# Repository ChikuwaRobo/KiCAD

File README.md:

# KiCAD
対応:User/Documents/KiCAD  
ユーザーライブラリを複数バージョンまとめて管理するためのリポジトリ｡

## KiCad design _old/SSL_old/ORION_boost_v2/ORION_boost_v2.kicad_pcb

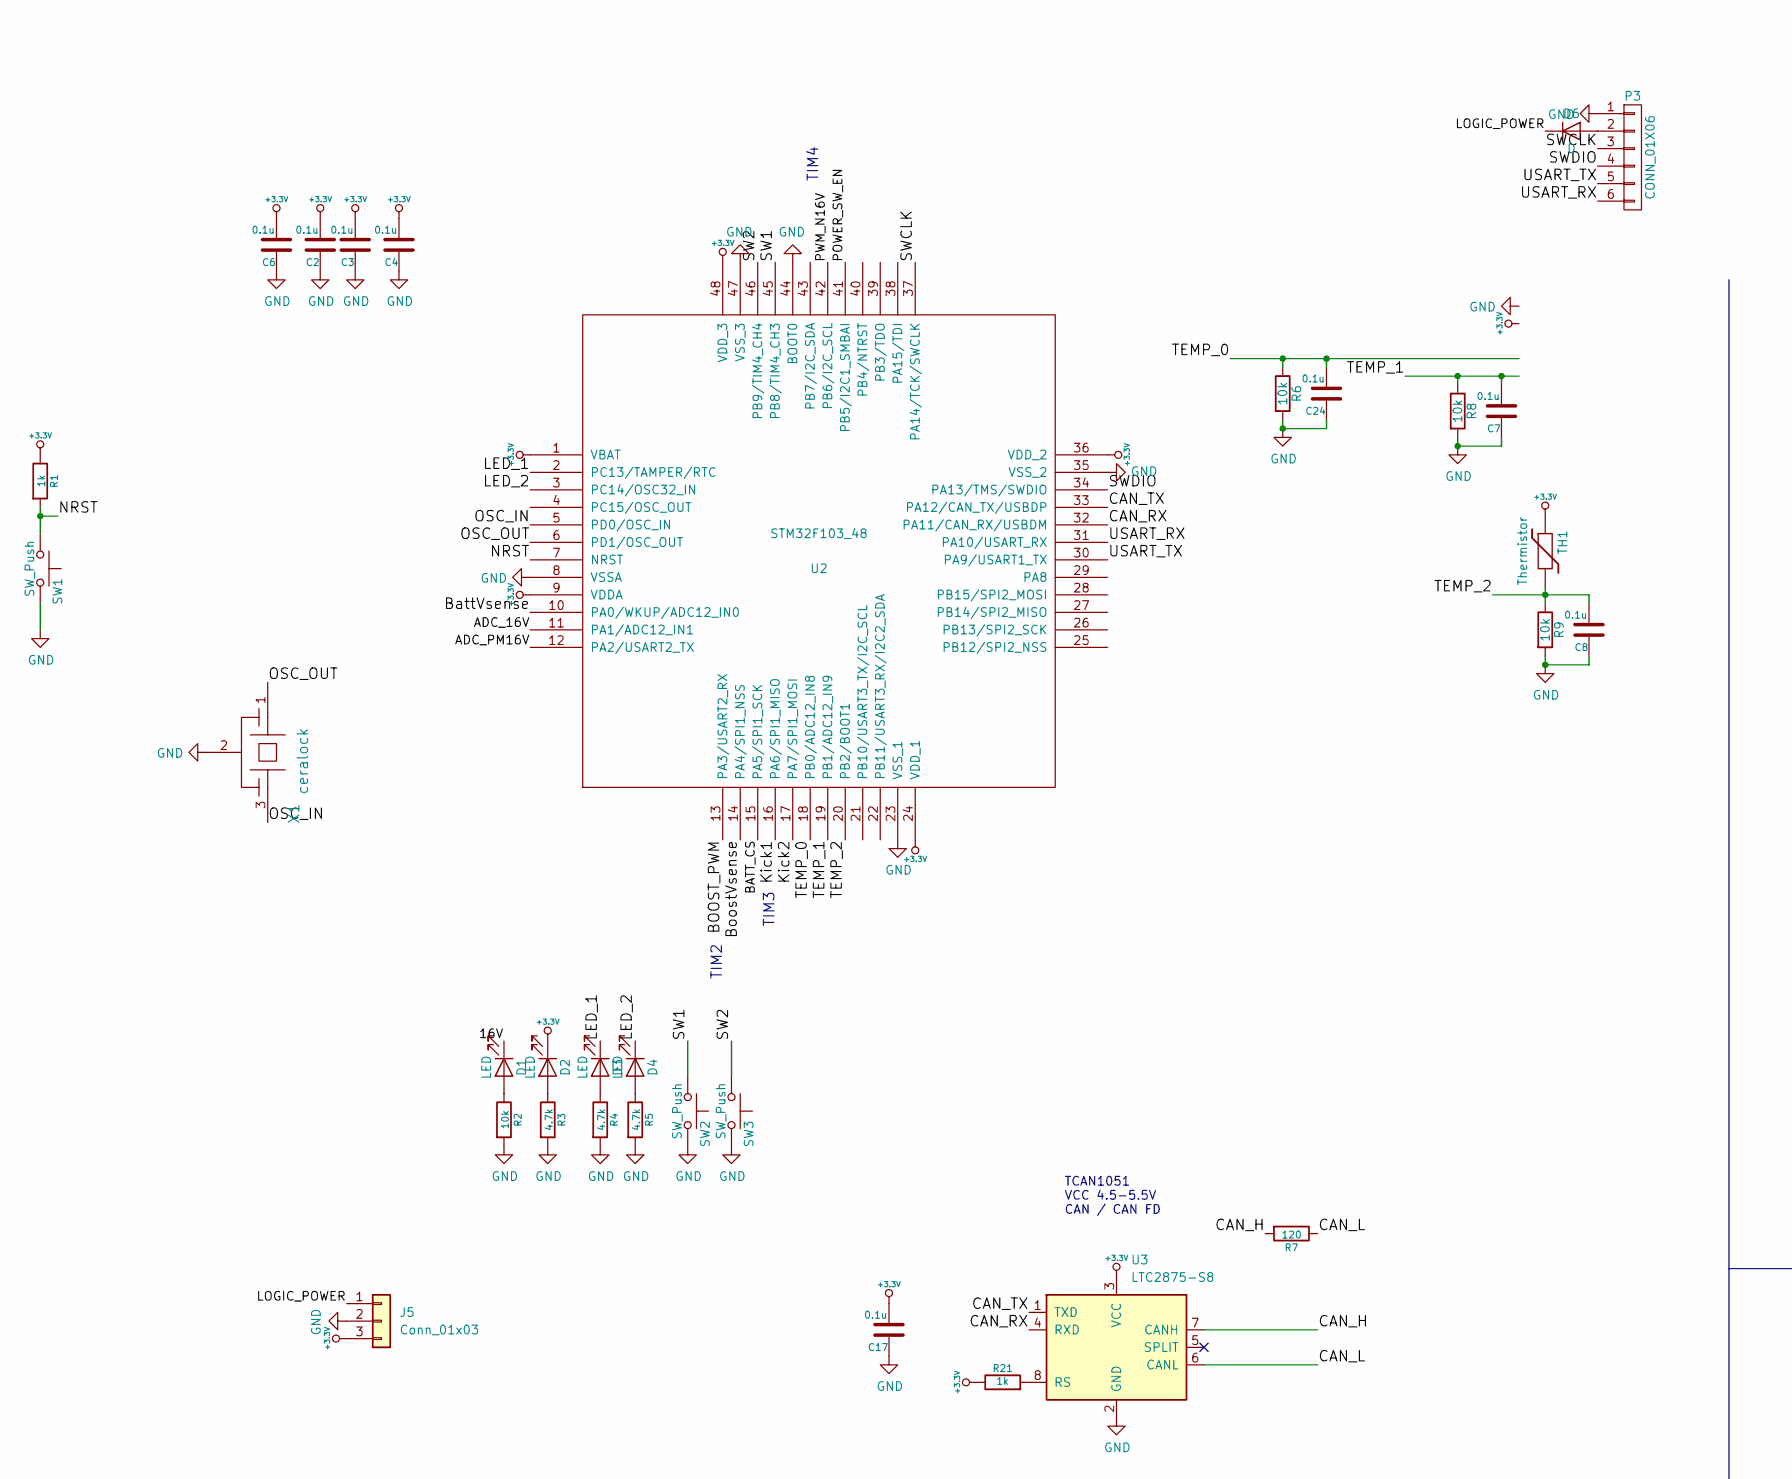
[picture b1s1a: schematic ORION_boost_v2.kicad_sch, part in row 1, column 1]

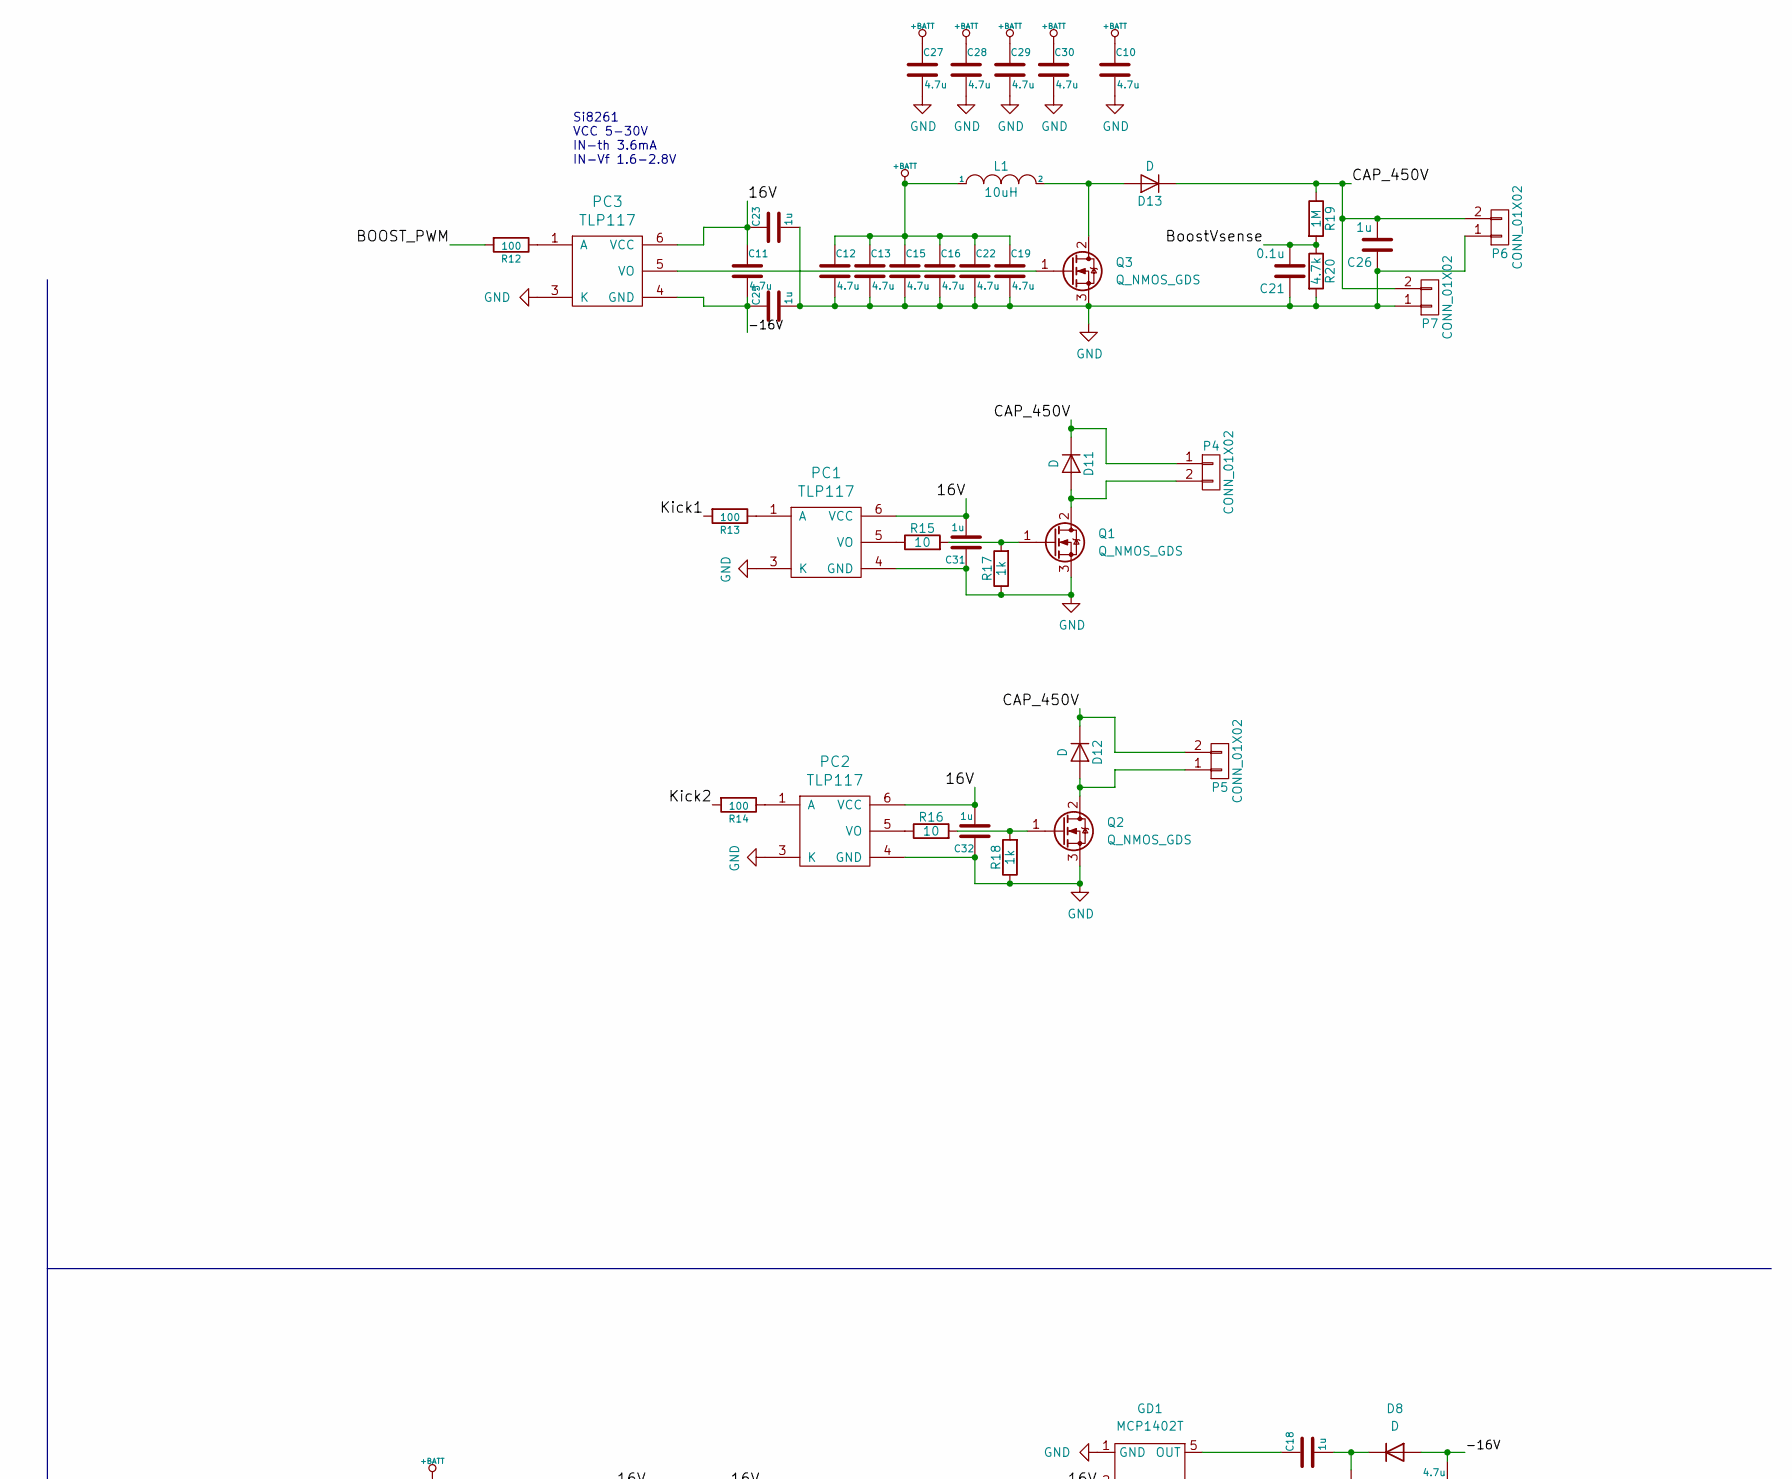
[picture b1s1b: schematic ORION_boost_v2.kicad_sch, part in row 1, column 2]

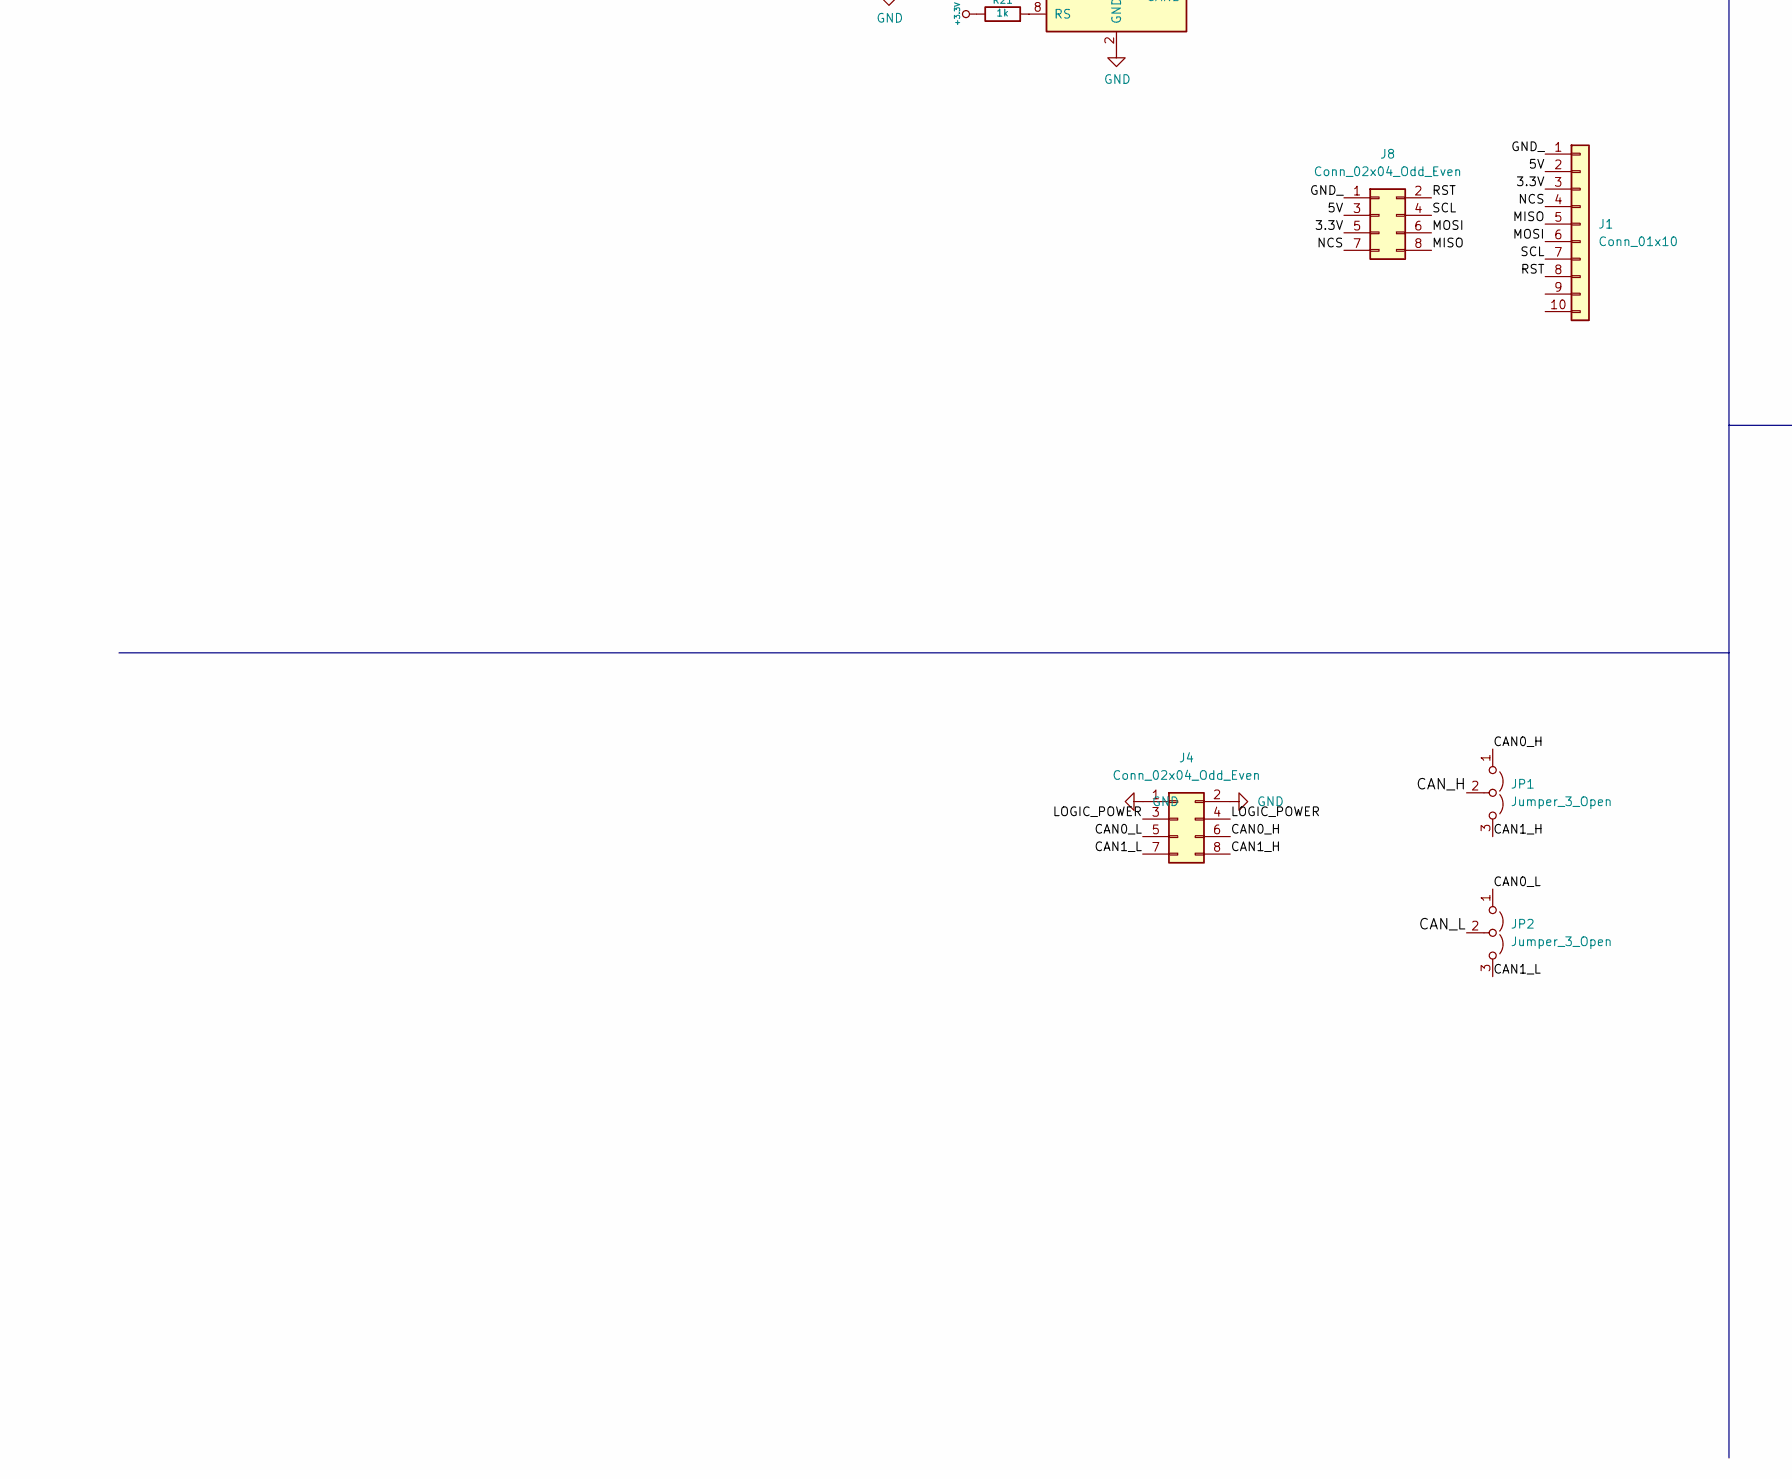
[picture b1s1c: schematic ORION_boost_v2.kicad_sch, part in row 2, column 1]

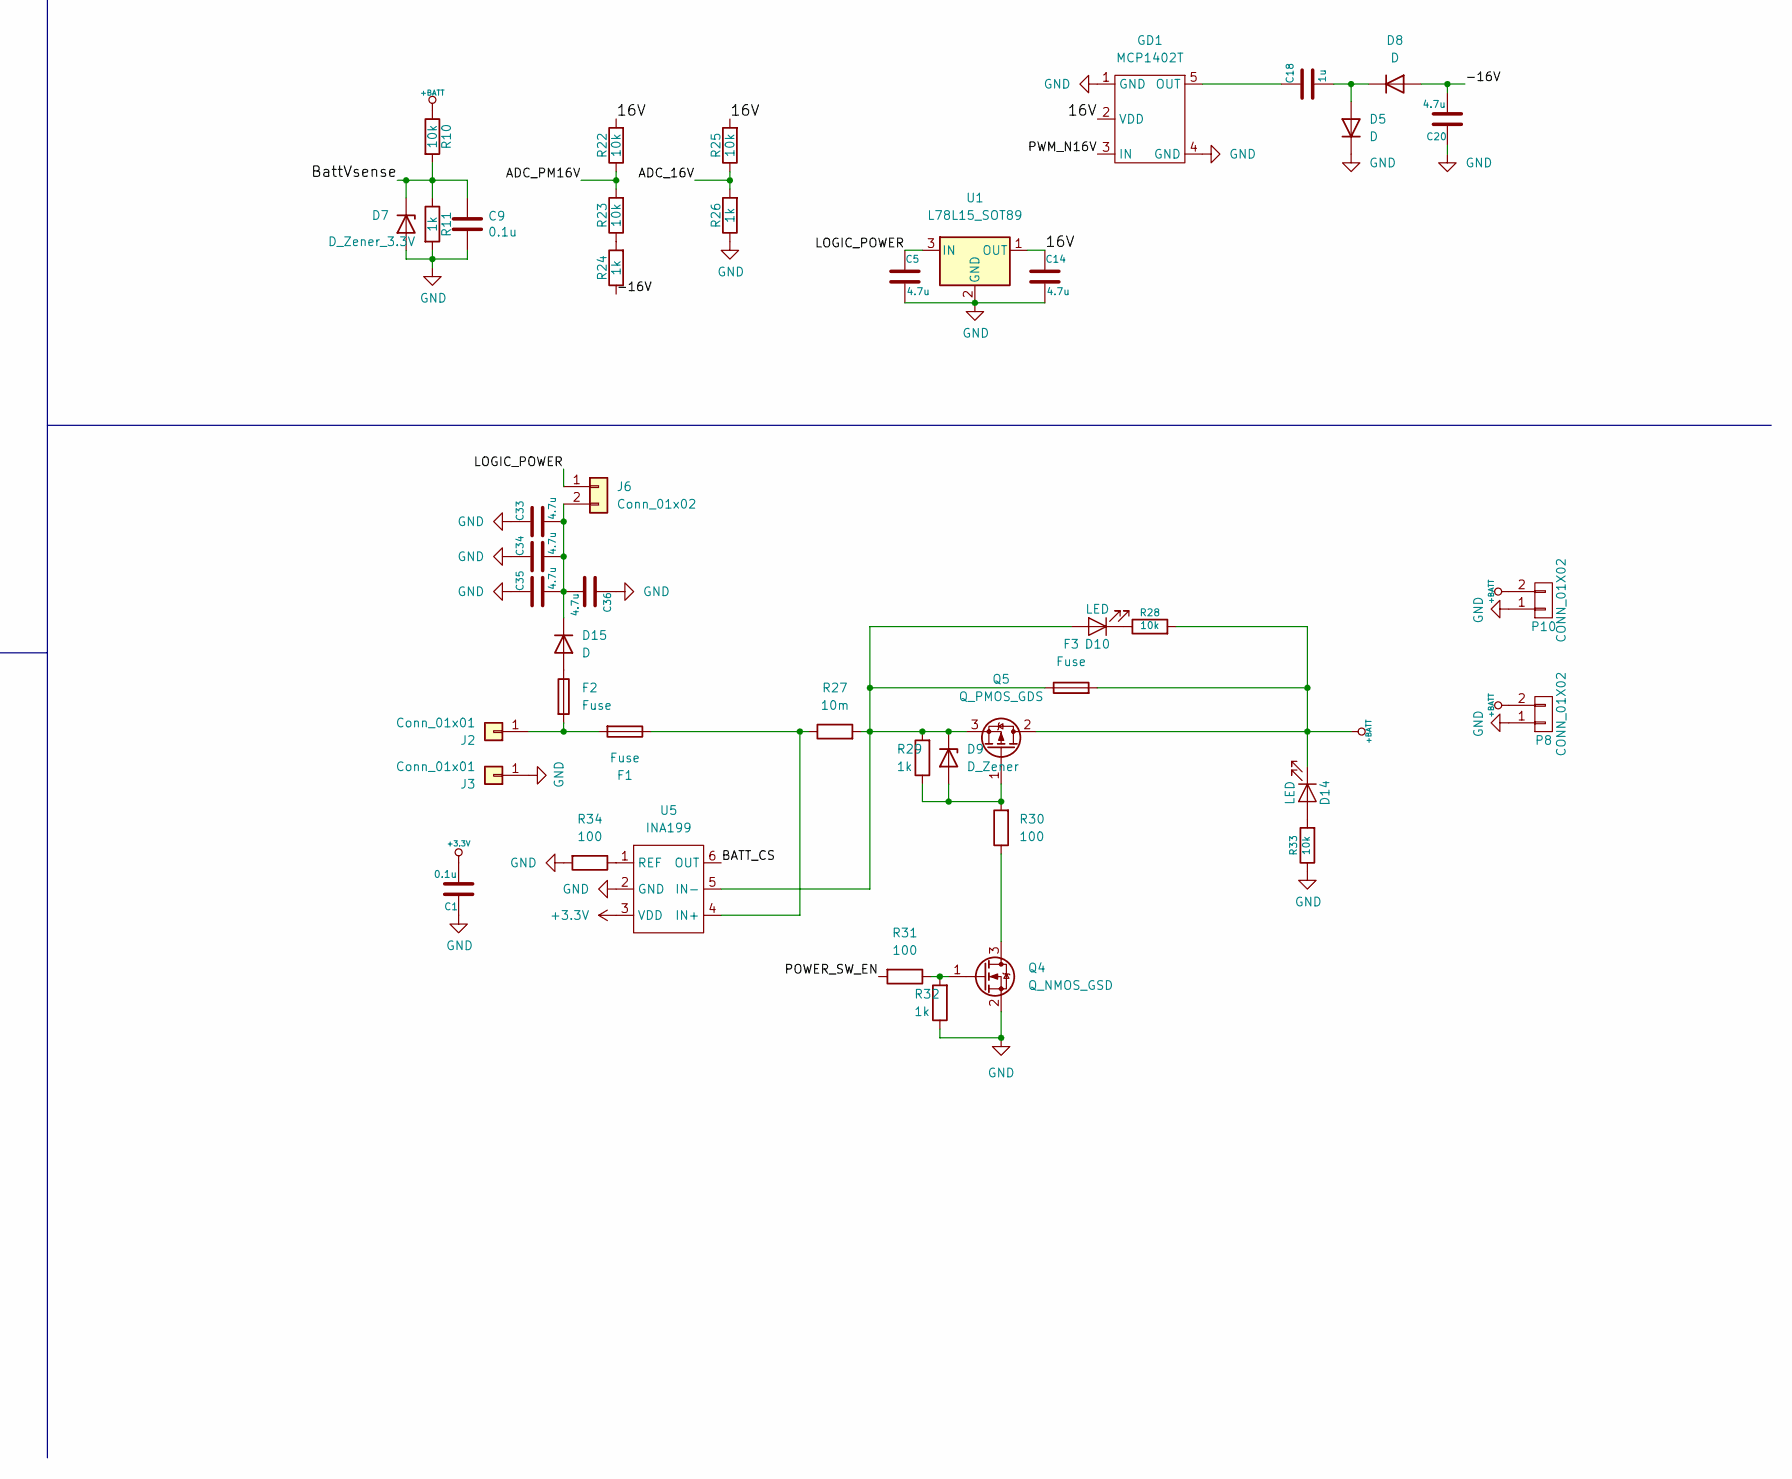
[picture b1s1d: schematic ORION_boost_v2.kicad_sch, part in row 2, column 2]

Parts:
C1, C2, C3, C4, C6, C7, C8, C9, C17, C21, C24: 0.1u; C_0603_1608Metric
C5, C10, C11, C14, C15, C16, C19, C20, C22, C27, C28, C29, C30, C33, C34, C35, C36: 4.7u; C_1206_3216Metric
C12, C13: 4.7u; CP_Radial_D10.0mm_P5.00mm
C18, C23, C25, C31, C32: 1u; C_0603_1608Metric
C26: 1u; C_Rect_L16.5mm_W5.0mm_P15.00mm_MKT
D1, D2, D3, D4, D10, D14: LED; LED_0603_1608Metric
D5, D6, D8: D; D_0603_1608Metric
D7: D_Zener_3.3V; D_0603_1608Metric
D9: D_Zener; D_0603_1608Metric_Pad1.05x0.95mm_HandSolder
D11, D12, D13: D; TO-252-2-RD
D15: D; D_MiniMELF
F1: Fuse; Reusable_Breaker_Top
F2, F3: Fuse; Fuse_1210_3225Metric
GD1: MCP1402T; SOT-23-5
J1: Conn_01x10; PinSocket_1x10_P2.54mm_Vertical
J2, J3: Conn_01x01; TestPoint_Plated_Hole_D4.0mm
J4, J8: Conn_02x04_Odd_Even; Hirose_DF11-8DP-2DSA_2x04_P2.00mm_Vertical
J5: Conn_01x03; VX07805-500
J6: Conn_01x02; JST_PH_B2B-PH-K_1x02_P2.00mm_Vertical
JP1, JP2: Jumper_3_Open; SolderJumper-3_P1.3mm_Open_RoundedPad1.0x1.5mm
L1: 10uH; L_Bourns_SRP1770TA_16.9x16.9mm
P3: CONN_01X06; ZH_B6B-ZR
P4, P5, P6, P7: CONN_01X02; Hirose_DF63M-2P-3.96DSA_1x02_P3.96mm_Vertical_pinless
P8, P10: CONN_01X02; AMASS_XT30U-M_1x02_P5.0mm_Vertical
PC1, PC2, PC3: TLP117; MFSOP6-5_4.4x3.6mm_P1.27mm
Q1, Q2: Q_NMOS_GDS; TO-252-2
Q3: Q_NMOS_GDS; TO-220F-3_Horizontal_TabDown_HV
Q4: Q_NMOS_GSD; SOT-23
Q5: Q_PMOS_GDS; TO-252-2
R1, R11, R17, R18, R24, R26, R29, R32: 1k; R_0603_1608Metric
R2, R28, R33: 10k; R_0603_1608Metric_Pad0.98x0.95mm_HandSolder
R3, R4, R5, R20: 4.7k; R_0603_1608Metric
R6, R8, R9, R10, R22, R23, R25: 10k; R_0603_1608Metric
R7: 120; R_0603_1608Metric
R12: 100; R_0603_1608Metric_Pad0.98x0.95mm_HandSolder
R13, R14, R30, R31, R34: 100; R_0603_1608Metric
R15, R16: 10; R_0603_1608Metric
R19: 1M; R_1206_3216Metric
R21: 1k; R_0603_1608Metric_Pad0.98x0.95mm_HandSolder
R27: 10m; R_1020_2550Metric
SW1, SW2, SW3: SW_Push; SW_Push_1P1T_NO_CK_KMR2
TH1: Thermistor; R_0603_1608Metric
U1: L78L15_SOT89; SOT-89-3
U2: STM32F103_48; LQFP-48_7x7mm_P0.5mm
U3: LTC2875-S8; SOIC-8_3.9x4.9mm_P1.27mm
U5: INA199; SOT-23-6
X1: ceralock; Resonator_SMD_Murata_CSTxExxV-3Pin_3.0x1.1mm

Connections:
+3.3V: C1.2, C2.2, C3.2, C4.2, C6.2, C17.2, D2.1 (K), J5.3, R1.1, R21.1, TH1.1, U2.1 (VBAT), U2.9 (VDDA), U2.24 (VDD_1), U2.36 (VDD_2), U2.48 (VDD_3), U3.3 (VCC), U5.3 (VDD)
+BATT: C10.1, C12.1, C13.1, C15.1, C16.1, C19.1, C22.1, C27.1, C28.1, C29.1, C30.1, D14.1 (K), F3.2, L1.1, P8.2, P10.2, Q5.2 (D), R10.1, R28.2
/3.3V: J1.3, J8.5
/5V: J1.2, J8.3
/16V: C11.1, C14.1, C23.1, C31.2, C32.2, D1.1 (K), GD1.2 (VDD), PC1.6 (VCC), PC2.6 (VCC), PC3.6 (VCC), R22.2, R25.2, U1.1 (OUT)
/-16V: C11.2, C20.2, C25.1, D8.2 (A), PC3.4 (GND), R24.1
/ADC_16V: R25.1, R26.2, U2.11 (PA1/ADC12_IN1)
/ADC_PM16V: R22.1, R23.2, U2.12 (PA2/USART2_TX)
/BATT_CS: U2.15 (PA5/SPI1_SCK), U5.6 (OUT)
/BOOST_PWM: R12.2, U2.13 (PA3/USART2_RX)
/BattVsense: C9.2, D7.1 (K), R10.2, R11.1, U2.10 (PA0/WKUP/ADC12_IN0)
/BoostVsense: C21.2, R19.2, R20.1, U2.14 (PA4/SPI1_NSS)
/CAN0_H: J4.6, JP1.1 (A)
/CAN0_L: J4.5, JP2.1 (A)
/CAN1_H: J4.8, JP1.3 (B)
/CAN1_L: J4.7, JP2.3 (B)
/CAN_H: JP1.2 (C), R7.2, U3.7 (CANH)
/CAN_L: JP2.2 (C), R7.1, U3.6 (CANL)
/CAN_RX: U2.32 (PA11/CAN_RX/USBDM), U3.4 (RXD)
/CAN_TX: U2.33 (PA12/CAN_TX/USBDP), U3.1 (TXD)
/CAP_450V: C26.2, D11.1 (K), D12.1 (K), D13.1 (K), P4.1, P5.2, P6.2, P7.2, R19.1
/GND_: J1.1, J8.1
/Kick1: R13.2, U2.16 (PA6/SPI1_MISO)
/Kick2: R14.2, U2.17 (PA7/SPI1_MOSI)
/LED_1: D3.1 (K), U2.2 (PC13/TAMPER/RTC)
/LED_2: D4.1 (K), U2.3 (PC14/OSC32_IN)
/LOGIC_POWER: C5.1, D6.1 (K), J4.3, J4.4, J5.1, J6.1, U1.3 (IN)
/MISO: J1.5, J8.8
/MOSI: J1.6, J8.6
/NCS: J1.4, J8.7
/NRST: R1.2, SW1.1, U2.7 (NRST)
/OSC_IN: U2.5 (PD0/OSC_IN), X1.3
/OSC_OUT: U2.6 (PD1/OSC_OUT), X1.1
/POWER_SW_EN: R31.2, U2.41 (PB5/I2C1_SMBAI)
/PWM_N16V: GD1.3 (IN), U2.42 (PB6/I2C_SCL)
/RST: J1.8, J8.2
/SCL: J1.7, J8.4
/SW1: SW2.1, U2.45 (PB8/TIM4_CH3)
/SW2: SW3.1, U2.46 (PB9/TIM4_CH4)
/SWCLK: P3.3, U2.37 (PA14/TCK/SWCLK)
/SWDIO: P3.4, U2.34 (PA13/TMS/SWDIO)
/TEMP_0: C24.2, R6.1, U2.18 (PB0/ADC12_IN8)
/TEMP_1: C7.2, R8.1, U2.19 (PB1/ADC12_IN9)
/TEMP_2: C8.2, R9.1, TH1.2, U2.20 (PB2/BOOT1)
/USART_RX: P3.6, U2.31 (PA10/USART_RX)
/USART_TX: P3.5, U2.30 (PA9/USART1_TX)
GND: C1.1, C2.1, C3.1, C4.1, C5.2, C6.1, C7.1, C8.1, C9.1, C10.2, C12.2, C13.2, C14.2, C15.2, C16.2, C17.1, C19.2, C20.1, C21.1, C22.2, C23.2, C24.1, C25.2, C26.1, C27.2, C28.2, C29.2, C30.2, C31.1, C32.1, C33.1, C34.1, C35.1, C36.1, D5.1 (K), D7.2 (A), GD1.1 (GND), GD1.4 (GND), J3.1, J4.1, J4.2, J5.2, P3.1, P6.1, P7.1, P8.1, P10.1, PC1.3 (K), PC1.4 (GND), PC2.3 (K), PC2.4 (GND), PC3.3 (K), Q1.3 (S), Q2.3 (S), Q3.3 (S), Q4.2 (S), R2.2, R3.2, R4.2, R5.2, R6.2, R8.2, R9.2, R11.2, R17.1, R18.1, R20.2, R26.1, R32.1, R33.1, R34.2, SW1.2, SW2.2, SW3.2, U1.2 (GND), U2.8 (VSSA), U2.23 (VSS_1), U2.35 (VSS_2), U2.44 (BOOT0), U2.47 (VSS_3), U3.2 (GND), U5.2 (GND), X1.2
unnamed: C18.1, GD1.5 (OUT)
unnamed: C18.2, D5.2 (A), D8.1 (K)
unnamed: D1.2 (A), R2.1
unnamed: D2.2 (A), R3.1
unnamed: D3.2 (A), R4.1
unnamed: D4.2 (A), R5.1
unnamed: D6.2 (A), P3.2
unnamed: D9.2 (A), Q5.1 (G), R29.1, R30.2
unnamed: D10.1 (K), R28.1
unnamed: D9.1 (K), D10.2 (A), F3.1, Q5.3 (S), R27.2, R29.2, U5.5 (IN-)
unnamed: D11.2 (A), P4.2, Q1.2 (D)
unnamed: D12.2 (A), P5.1, Q2.2 (D)
unnamed: D13.2 (A), L1.2, Q3.2 (D)
unnamed: D14.2 (A), R33.2
unnamed: D15.2 (A), F2.1
unnamed: F1.1, R27.1, U5.4 (IN+)
unnamed: F1.2, F2.2, J2.1
unnamed: C33.2, C34.2, C35.2, C36.2, D15.1 (K), J6.2
unnamed: PC1.1 (A), R13.1
unnamed: PC1.5 (VO), R15.1
unnamed: PC2.1 (A), R14.1
unnamed: PC2.5 (VO), R16.1
unnamed: PC3.1 (A), R12.1
unnamed: PC3.5 (VO), Q3.1 (G)
unnamed: Q1.1 (G), R15.2, R17.2
unnamed: Q2.1 (G), R16.2, R18.2
unnamed: Q4.1 (G), R31.1, R32.2
unnamed: Q4.3 (D), R30.1
unnamed: R21.2, U3.8 (RS)
unnamed: R23.1, R24.2
unnamed: R34.1, U5.1 (REF)

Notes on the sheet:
Si8261 VCC 5-30V IN-th 3.6mA IN-Vf 1.6-2.8V
TIM3
TIM4
TCAN1051 VCC 4.5-5.5V CAN / CAN FD
TIM2

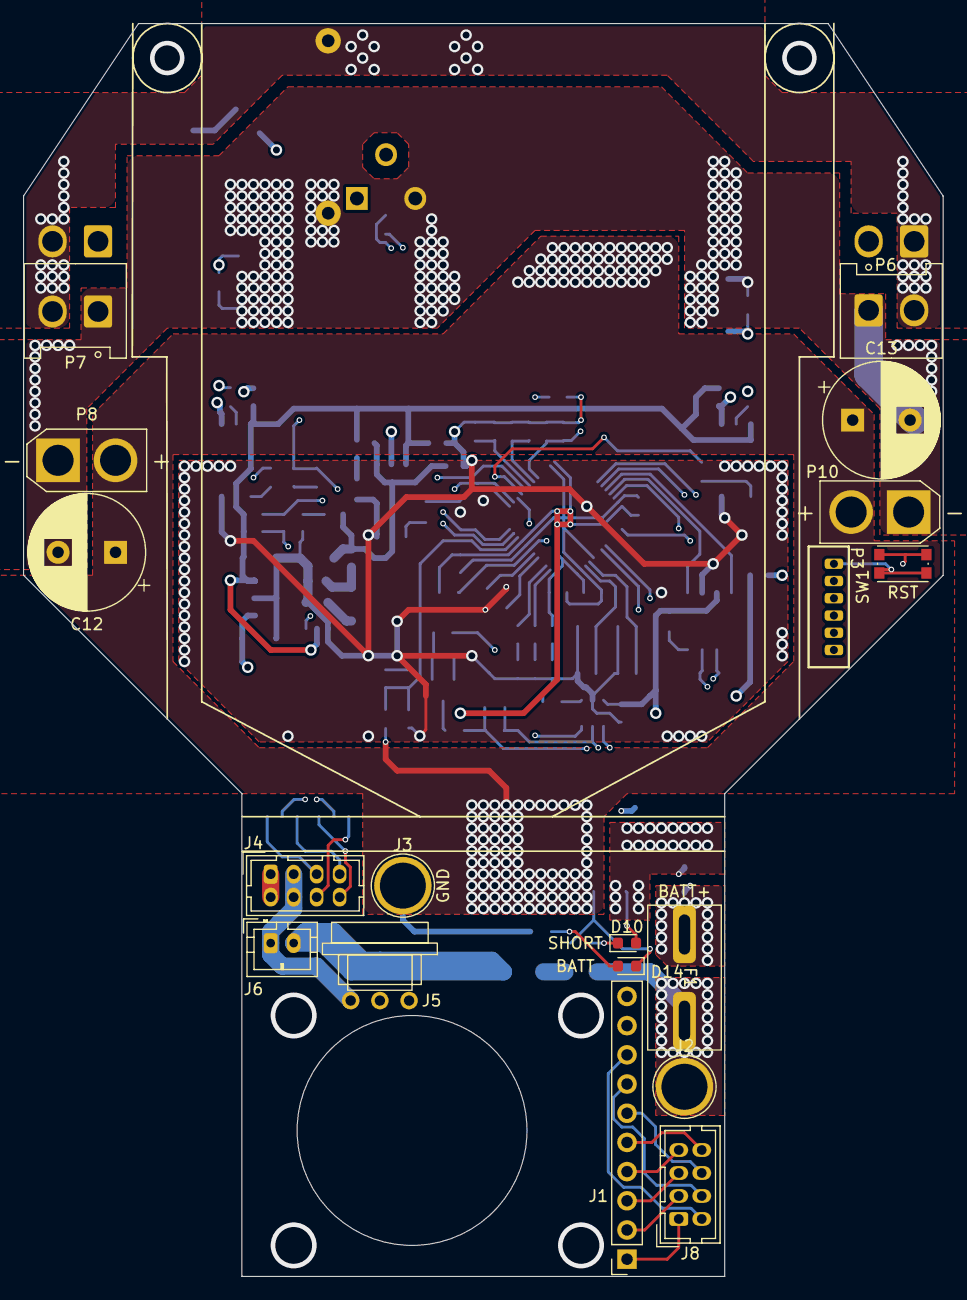
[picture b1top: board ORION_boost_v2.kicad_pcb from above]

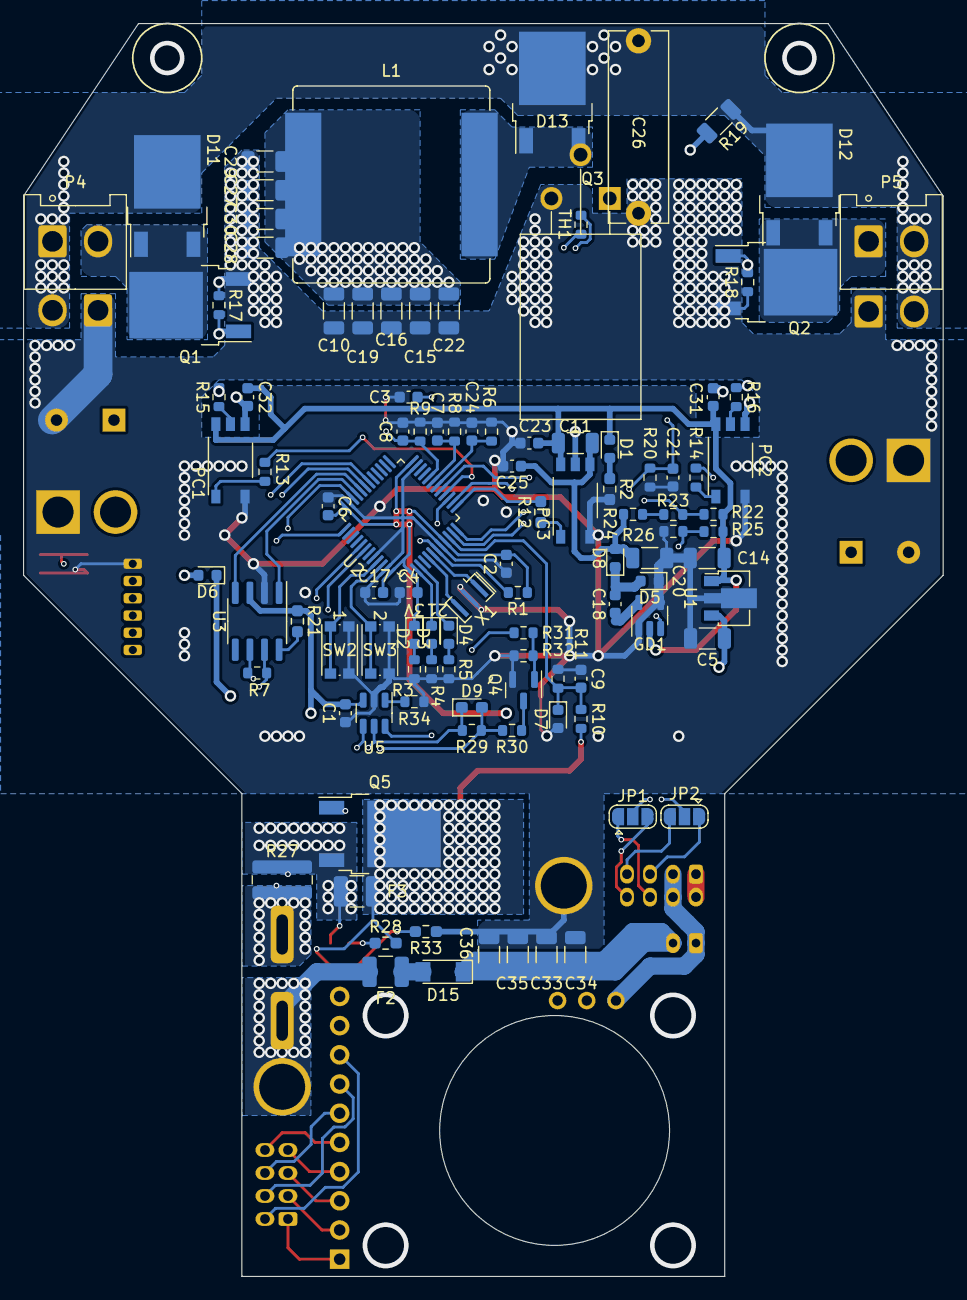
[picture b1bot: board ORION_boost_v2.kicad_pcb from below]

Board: 4 copper layers, 80.0 x 109.0 mm, 123 parts (105 on the bottom side), 78 nets.

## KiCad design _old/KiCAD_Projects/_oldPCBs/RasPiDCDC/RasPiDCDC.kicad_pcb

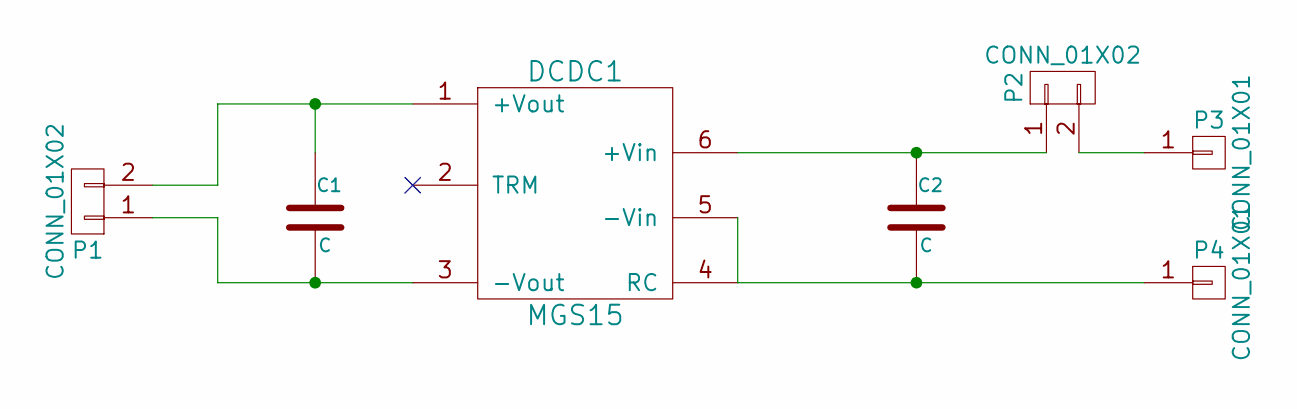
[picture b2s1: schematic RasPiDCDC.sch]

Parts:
C1, C2: C; C_Radial_D10_L20_P5
DCDC1: MGS15; MGS30
P1, P2: CONN_01X02; XA_2T
P3, P4: CONN_01X01; 1pin

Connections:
unnamed: C1.1, DCDC1.1 (+Vout), P1.2
unnamed: C1.2, DCDC1.3 (-Vout), P1.1
unnamed: C2.1, DCDC1.6 (+Vin), P2.1
unnamed: C2.2, DCDC1.4 (RC), DCDC1.5 (-Vin), P4.1
unnamed: P2.2, P3.1

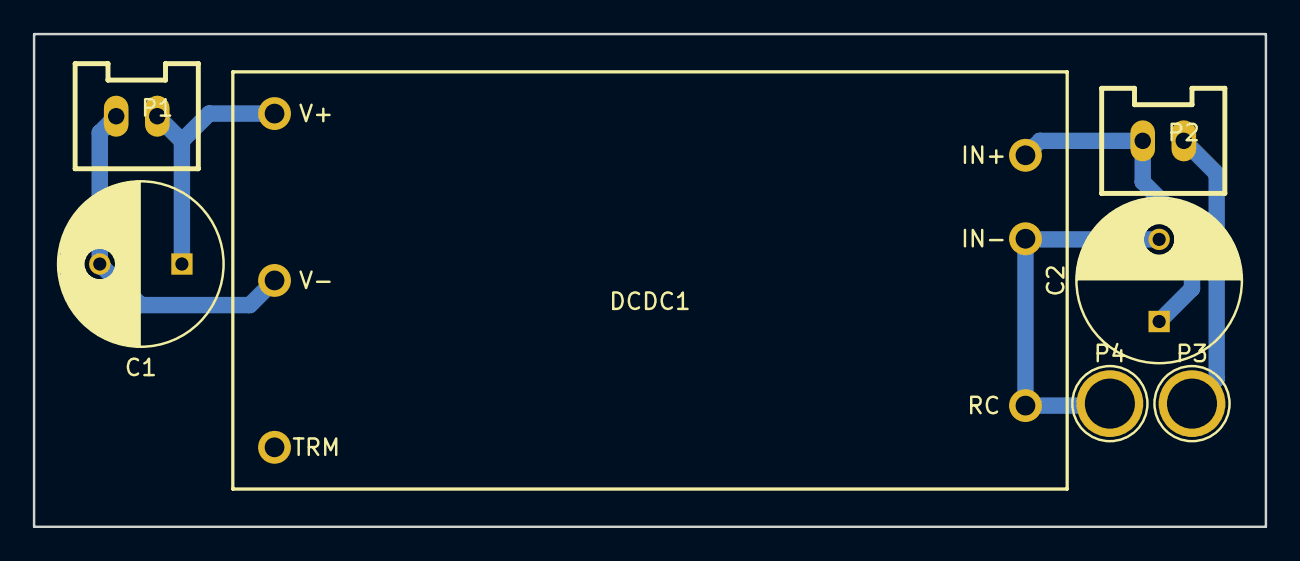
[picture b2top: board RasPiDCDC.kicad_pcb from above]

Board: 2 copper layers, 75.0 x 30.0 mm, 7 parts (0 on the bottom side), 5 nets.

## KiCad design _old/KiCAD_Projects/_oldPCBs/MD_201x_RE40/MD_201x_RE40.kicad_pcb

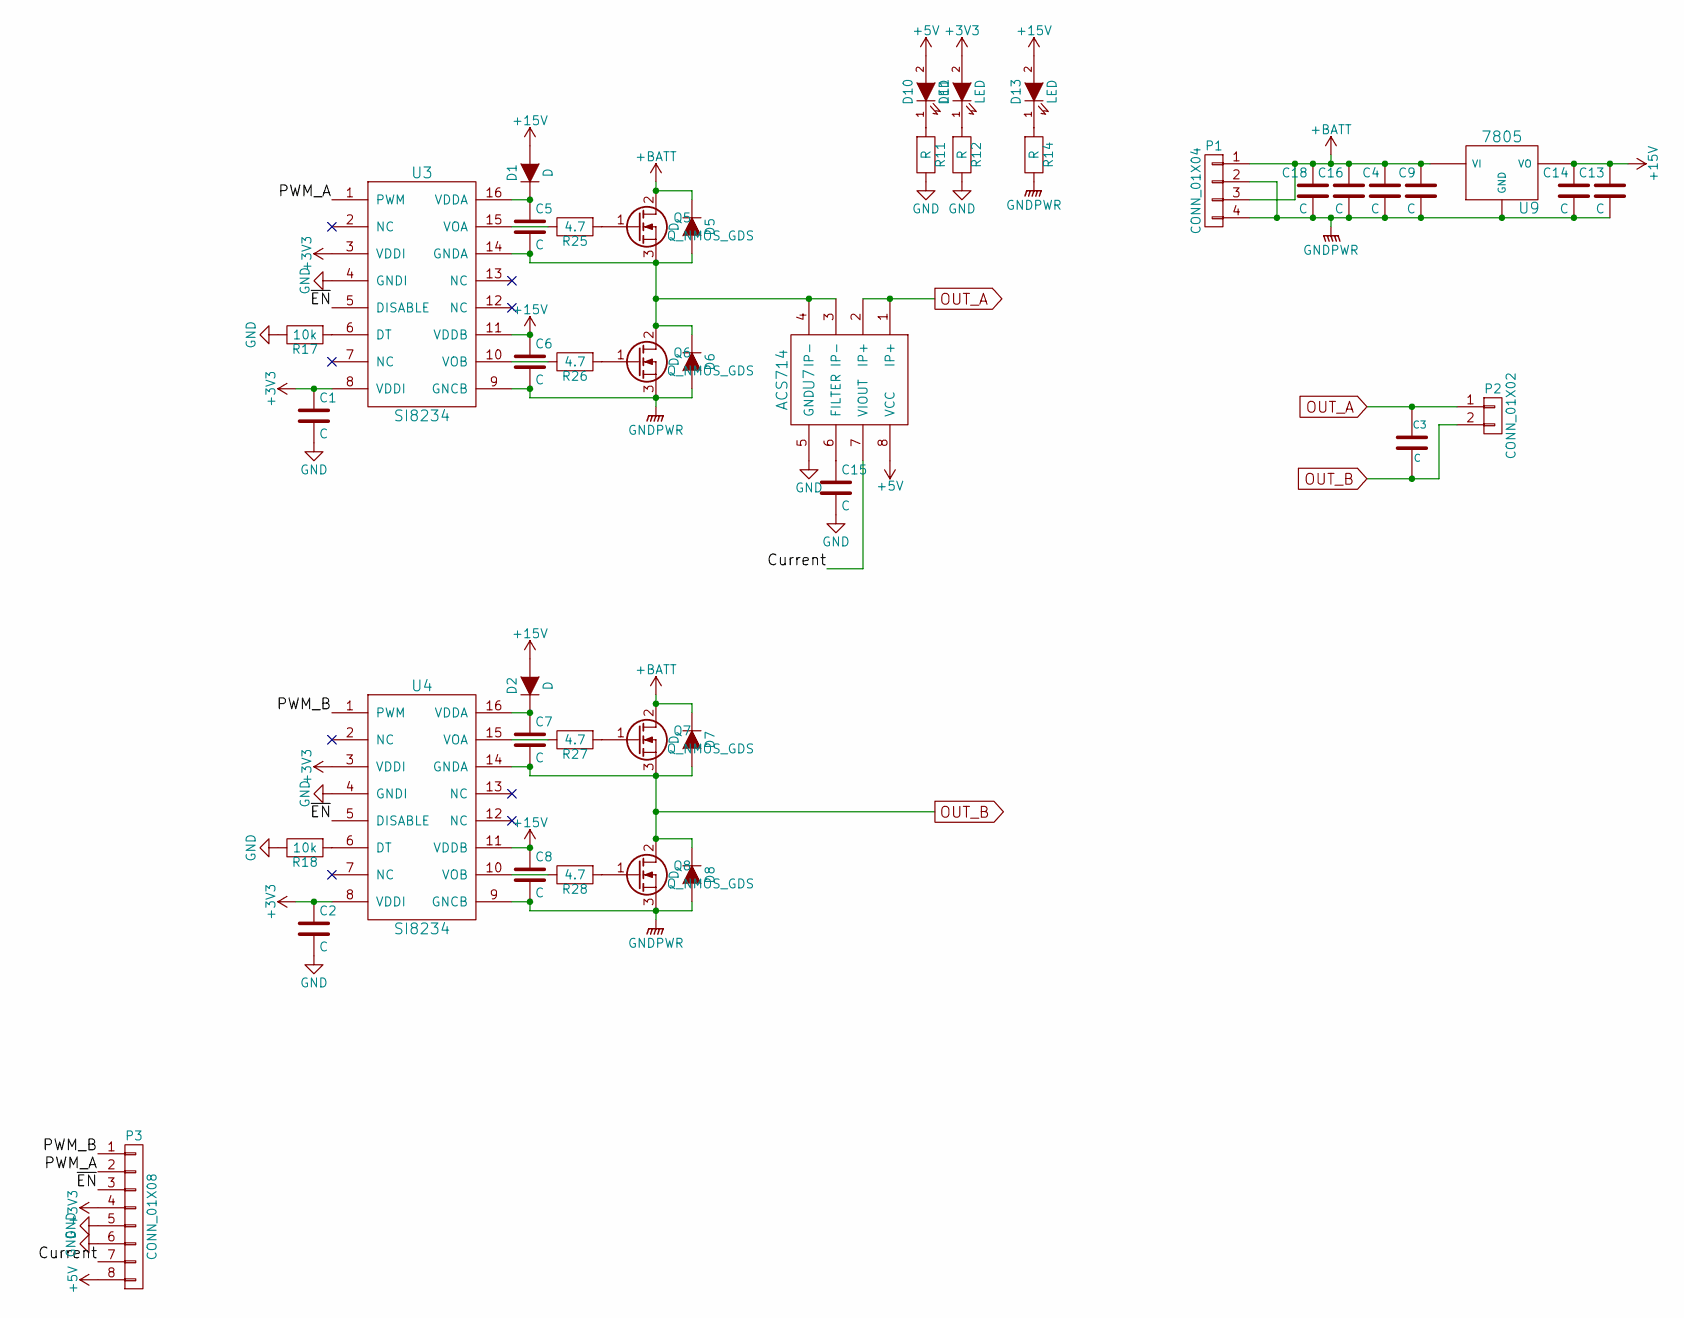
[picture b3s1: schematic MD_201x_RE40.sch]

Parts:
C1, C2, C3, C14, C15: C; C0603K
C4, C9, C13, C16, C18: C; C_Radial_D8_L11.5_P3.5
C5, C6, C7, C8: C; C1206K
D1, D2, D5, D6, D7, D8: D; MiniMELF_Standard
D10, D11, D13: LED; LED-3MM
P1: CONN_01X04; D-3500D_4S
P2: CONN_01X02; D-3200S_2
P3: CONN_01X08; Socket_Strip_Straight_1x08
Q5, Q6, Q7, Q8: Q_NMOS_GDS; SOT-404
R11, R12, R14: R; 0204_2f7
R17, R18: 10k; 0204_2f7
R25, R26, R27, R28: 4.7; 0207_2f10
U3, U4: SI8234; SOIC-16_3.9x9.9mm_Pitch1.27mm
U7: ACS714; DIP-8_W7.62mm
U9: 7805; SOT-223_regul

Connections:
+3V3: C1.1, C2.1, D11.2 (A), P3.4, U3.3 (VDDI), U3.8 (VDDI), U4.3 (VDDI), U4.8 (VDDI)
+5V: D10.2 (A), P3.8, U7.8 (VCC)
+15V: C6.1, C8.1, C13.1, C14.1, D1.2 (A), D2.2 (A), D13.2 (A), U3.11 (VDDB), U4.11 (VDDB), U9.VO
+BATT: C4.1, C9.1, C16.1, C18.1, D5.1 (K), D7.1 (K), P1.1, P1.3, Q5.2 (D), Q7.2 (D), U9.VI
/Current: P3.7, U7.7 (VIOUT)
/PWM_A: P3.2, U3.1 (PWM)
/PWM_B: P3.1, U4.1 (PWM)
/~EN: P3.3, U3.5 (DISABLE), U4.5 (DISABLE)
GND: C1.2, C2.2, C15.2, P3.5, P3.6, R11.2, R12.2, R17.2, R18.2, U3.4 (GNDI), U4.4 (GNDI), U7.5 (GND)
GNDPWR: C4.2, C6.2, C8.2, C9.2, C13.2, C14.2, C16.2, C18.2, D6.2 (A), D8.2 (A), P1.2, P1.4, Q6.3 (S), Q8.3 (S), R14.2, U3.9 (GNCB), U4.9 (GNCB), U9.GND
unnamed: C5.1, D1.1 (K), U3.16 (VDDA)
unnamed: C5.2, D5.2 (A), D6.1 (K), Q5.3 (S), Q6.2 (D), U3.14 (GNDA), U7.3 (IP-), U7.4 (IP-)
unnamed: C7.1, D2.1 (K), U4.16 (VDDA)
unnamed: C15.1, U7.6 (FILTER)
unnamed: D10.1 (K), R11.1
unnamed: D11.1 (K), R12.1
unnamed: D13.1 (K), R14.1
unnamed: Q5.1 (G), R25.1
unnamed: Q6.1 (G), R26.1
unnamed: Q7.1 (G), R27.1
unnamed: Q8.1 (G), R28.1
unnamed: R17.1, U3.6 (DT)
unnamed: R18.1, U4.6 (DT)
unnamed: R25.2, U3.15 (VOA)
unnamed: R26.2, U3.10 (VOB)
unnamed: R27.2, U4.15 (VOA)
unnamed: R28.2, U4.10 (VOB)
OUT_A: C3.1, P2.1, U7.1 (IP+), U7.2 (IP+)
OUT_B: C3.2, C7.2, D7.2 (A), D8.1 (K), P2.2, Q7.3 (S), Q8.2 (D), U4.14 (GNDA)

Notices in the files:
parts and their libraries:
Copyright 2021 Accelerated Designs. All rights reserved.
